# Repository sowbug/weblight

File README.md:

# WebLight

A USB-controlled LED designed for the
[WebUSB API](https://wicg.github.io/webusb/).

Try the web app
===
Have a WebLight device already?  
Launch the web app here:  
https://sowbug.github.io/weblight/

What does the javascript look like to write color values?  
Check out [software/src/weblight-card.html](https://github.com/sowbug/weblight/blob/master/software/src/weblight-card.html)

Developing WebLight Devices
===

Toolchain/environment setup
---

* Install avr-gcc. On Windows, download avr-gcc from
http://andybrown.me.uk/2015/03/08/avr-gcc-492/. Make sure you've
installed a base MinGW and MSYS system or equivalent, and have them in
your system path. On Linux, try something like `sudo apt-get install
gcc-avr binutils-avr gdb-avr avr-libc avrdude`. On OS X,
[CrossPack](https://www.obdev.at/products/crosspack/index.html) works.
* Install libusb. `sudo apt-get install libusb-dev` works on
  Linux, and `brew install libusb libusb-compat` works on OS X.
* Install pyusb. `sudo apt-get install python-usb` on Linux, or `sudo pip
  install pyusb` on other platforms.
* Build and install the
  [micronucleus command-line tool](https://github.com/micronucleus/micronucleus/tree/master/commandline)
  to be able to upload to the ATTiny85. Have it somewhere in your PATH. Don't forget [the udev rule](https://raw.githubusercontent.com/micronucleus/micronucleus/master/commandline/49-micronucleus.rules) if needed.
* Copy the files in `udev` to `/etc/udev/rules.d/` and then `sudo
  udevadm control --reload-rules`.

Programming a newly built board
---

* Connect a 6-pin AVR programmer. Note that if you've built the
  production version of the board, you'll need either an SOIC-8 clip
  manually wired for the ATtiny85, or else a
  [ProtoProg](http://protofusion.org/wordpress/2013/05/open-hardware-pogo-pin-programmer/)
  programming
  adapter. [This is the project I ordered](https://oshpark.com/shared_projects/fqvxyzoH)
  from OSH Park, and you'll want [0.68mm diameter, 16mm length pogo
  pins](http://www.ebay.com/sch/i.html?_trksid=p3984.m570.l1313.TR0.TRC0&_nkw=%09+10pcs+P50-J1+Dia+0.68mm+Length+16mm+75g+Spring+Test.&_sacat=0&_from=R40), probably from eBay.
* `cd firmware`
* Configure the makefile to talk to your type of programmer (default
usbtiny).
* `make factory` Now you have a bootloader-ready board with no firmware.
* Disconnect the programmer and plug it into a USB port.
* `make clean upload`

Mass-producing boards
---

This clones the complete firmware from an existing device. For
convenience, a relatively stable version of that complete firmware
image is already here in the repository (full-[version].hex). If you
overwrite it, we'll assume you know what you're doing.

1. Make one device using the instructions from the previous section.
1. Unplug from USB and attach to programmer.
1. `cd firmware`
1. `make create_full` This clones the firmware of the board you just
built.
1. Attach your next board to the programmer.
1. `make factory_mp`
1. Repeat last two steps for all remaining boards.

Development
---

1. In the `firmware` directory, `make clean upload`.
1. Plug in the board. After a few moments you should see `Micronucleus
   done. Thank you!`
1. Now the lights on the board should run a startup sequence.
1. Using `lsusb` you should see something like `Bus 001 Device 006: ID
   1209:a800 InterBiometrics`.

Usage
---

1. Install [PyUSB](http://walac.github.io/pyusb/). `sudo pip install
pyusb==1.0.0.b2`
1. From the base directory of the weblight project,
`./commandline/wlctl 800000` will give you a medium-brightness red
light (it uses CSS-style RGB color format).
1. `--help` for more options.

BOM for production (not developer) circuit
---

The best results are with an ENIG finish 2.0mm thickness PCB. If you're just prototyping, 1.6mm will work, but you'll want to put some thick solder on the USB leads to bulk them up a bit. Even then, the fit in the USB socket will be loose. ENIG takes longer to wear out than regular HASL.

The board measures 12mm x 41.1734mm x 2.0mm.

* C1: 1uF 0805 capacitor (DigiKey 311-1365-1-ND)
* C2: 0.1uF 0805 capacitor (DigiKey 311-1142-1-ND)
* D1, D2: 3.6V SOD-323 Zener diode. I successfully used BZT52C3V6S-7-F and MM3Z3V6T1G (DigiKey MM3Z3V6T1GOSCT-ND). According to [V-USB Hardware Considerations](http://vusb.wikidot.com/hardware), they should be "those that look like 1N4148 (usually 500 mW or less)"
* D3, D4: low forward-voltage SOD-323 diode (0.4-volt or less forward voltage so that the supply to the LEDs is higher than 4.5 volts). I have successfully used Toshiba 1SS367 (forward voltage about 0.3V, DigiKey 1SS367H3FCT-ND).
* LED1, LED2: APA102C LED (Real versions of these are not especially easy to find)
* R1: 1.5K 0805 resistor (DigiKey 311-1.5KARCT-ND)
* R2, R3: 68 0805 resistor (DigiKey 311-68ARCT-ND)
* R4: 10K 0805 resistor (DigiKey 311-10KARCT-ND)
* U1: ATtiny85 ATTINY85-20SU (DigiKey ATTINY85-20SURCT-ND)

Tips
---

* In addition to `wlctl` in the `commandline` directory, there is
`lswusb`, which attempts to parse WebUSB descriptors. This utility
will help you when you're developing your own WebUSB-compatible
device.

FAQ
===

* **What is WebUSB?** It's a [new web
  standard](https://reillyeon.github.io/webusb/) that makes it
  easy to write a USB driver once (in JavaScript) and have it work
  everywhere that WebUSB is supported.

* **Aren't there already a lot of USB-controlled lights out there?**
  Yes, it's more or less a rite of passage in hobbyist electronics to
  make some kind of blinking light. The purpose of this project was to
  design a very simple WebUSB device that might actually be useful.

* **You said "useful" in the prior answer. Please define that.** A
  WebUSB-enabled light can alert you of interesting things, like a
  broken continuous build, a service interruption, or yet another
  crash in the price of bitcoin.

* **Which board should I build?** If you're interested in hacking on
  the firmware, build
  [`weblight_developer.brd`](https://github.com/sowbug/weblight/blob/master/hardware/weblight_developer.brd). This
  one has a few more features that make firmware development more convenient. Otherwise if
  you just want a device to play with, build
  [`weblight.brd`](https://github.com/sowbug/weblight/blob/master/hardware/apa102/weblight.brd). That
  one is more compact, but it requires the ProtoProg ISP adapter, rather than the more common
  AVRISP 6-pin adapter. Both designs use 0805 SMT components. Either board can be ordered from [OSH Park](https://oshpark.com/) or [Seeed](https://www.seeedstudio.com/service/). Note that if you manufacture with a
  standard 1.6mm PCB, you'll have to solder the contacts to give them enough thickness to connect. For end-user
  boards, 2.0mm or 2.4mm will fit better in USB sockets, and ENIG finish will last longer without tarnishing.

* **I don't want to build a board, but I'd like one. Will you sell me one?** I don't have plans to mass-produce boards for sale. But if you're interested in getting one, [subscribe to notifications for this issue](https://github.com/sowbug/weblight/issues/31).

* **I remember reading something about Origin Trials. What does that have to do with WebUSB?** Chrome 61 and beyond ship with WebUSB, so if your users are running up-to-date Chrome, you're all set! But in case you're curious, the Chrome team has a system called Origin Trials for gathering real developer feedback on provisional APIs. Go to https://bit.ly/OriginTrials to learn more.

Acknowledgments
===

* Jenna Fox ([bluebie](https://github.com/bluebie)) and Tim ([cpldcpu](https://github.com/cpldcpu/)) for micronucleus advice. (Update December 2016: [Tim's article about SK9822](https://cpldcpu.com/2016/12/13/sk9822-a-clone-of-the-apa102/).)
* bobhackmelb on freenode for advice on PCB manufacturing, specifically thickness.
* [Passerby](http://electronics.stackexchange.com/users/17178/passerby) for help [reverse-engineering](http://electronics.stackexchange.com/questions/209941/two-sided-connectorless-usb-on-a-pcb) the double-sided USB connector.
* [gerblook.org](http://gerblook.org/) for an awesome Gerber visualizer.
* [Lars Knudsen](https://github.com/larsgk) for keeping docs up to date.

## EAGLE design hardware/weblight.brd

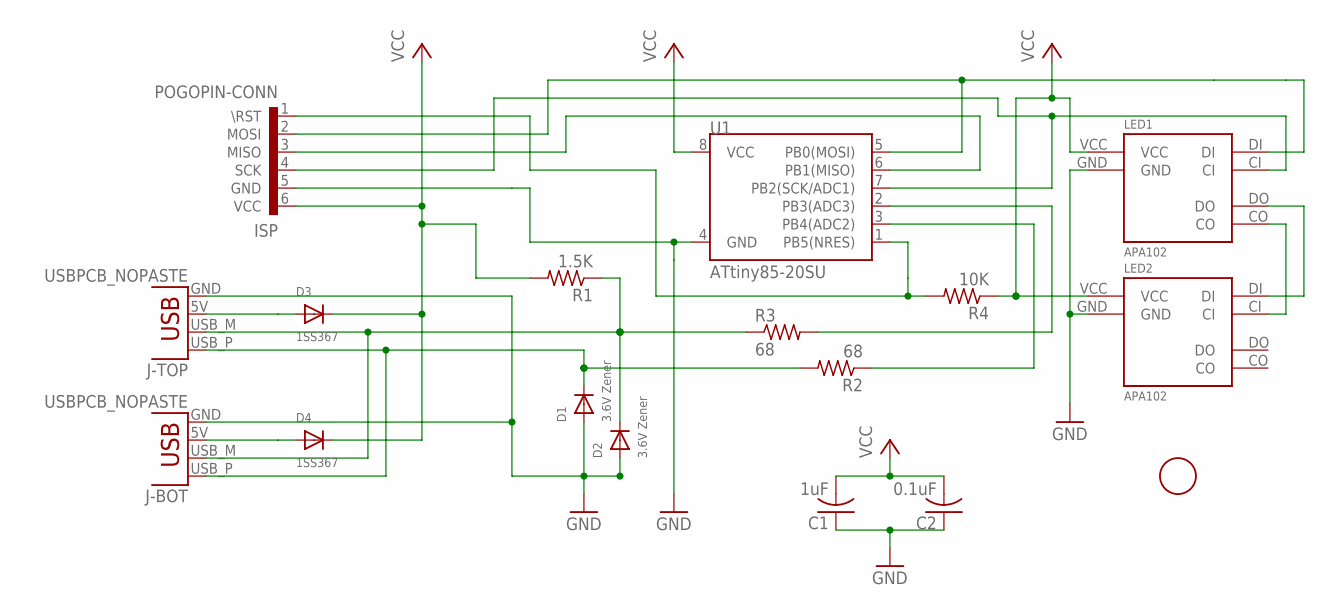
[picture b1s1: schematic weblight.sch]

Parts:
C1: 1uF; C0805
C2: 0.1uF; C0805
D1, D2: 3.6V Zener; SOD-323
D3, D4: 1SS367; SOD-323
FID1: FIDUCIAL; FIDUCIAL_1MM
ISP: POGOPIN-CONN; POGOPROG-CONN-OH-SMALLERVIAS-NOCREAM
J-BOT: USBPCB_NOPASTE; USB-A-PCB-NOPASTE
J-TOP: USBPCB_NOPASTE; USB-A-PCB-NOPASTE
LED1, LED2: APA102
R1: 1.5K; R0805
R2, R3: 68; R0805
R4: 10K; R0805
U1: ATtiny85-20SU; SO08-EIAJ

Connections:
5V-BOT: D4.A, J-BOT.5V (VBUS)
5V-TOP: D3.A, J-TOP.5V (VBUS)
CLK_1/SCK: ISP.4 (SCK), LED1.CI, U1.7 (PB2(SCK/ADC1))
CLK_2: LED1.CO, LED2.CI
DIN_1/MOSI: ISP.2 (MOSI), LED1.DI, U1.5 (PB0(MOSI))
DIN_2: LED1.DO, LED2.DI
GND: C1.1, C2.1, D1.A, D2.A, ISP.5 (GND), J-BOT.GND, J-TOP.GND, LED1.GND, LED2.GND, U1.4 (GND)
MISO: ISP.3 (MISO), U1.6 (PB1(MISO))
N_RESET: ISP.1 (\RST), R4.2, U1.1 (PB5(NRES))
USB_D_MINUS: R3.2, U1.2 (PB3(ADC3))
USB_D_MINUS_RAW: D2.C, J-BOT.USB_M (D-), J-TOP.USB_M (D-), R1.1, R3.1
USB_D_PLUS: R2.1, U1.3 (PB4(ADC2))
USB_D_PLUS_RAW: D1.C, J-BOT.USB_P (D+), J-TOP.USB_P (D+), R2.2
VCC: C1.2, C2.2, D3.C, D4.C, ISP.6 (VCC), LED1.VCC, LED2.VCC, R1.2, R4.1, U1.8 (VCC)

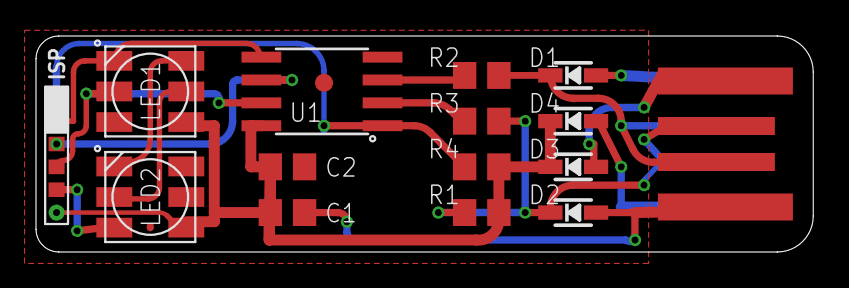
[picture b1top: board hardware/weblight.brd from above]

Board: 2 copper layers, 43.2 x 12.0 mm, 17 parts (1 on the bottom side), 14 nets.

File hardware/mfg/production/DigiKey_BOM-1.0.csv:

Digi-Key Part Number,Manufacturer,Manufacturer Part Number,Customer Reference,Quantity 1,Quantity 2,Quantity 3,Mfg Std Lead Time,Description,Comments,RoHS Status,Lead Free Status,REACH Status
311-1365-1-ND,YAGEO (VA),CC0805KKX7R7BB105,C1,1,0,0,21 Weeks,CAP CER 1UF 16V X7R 0805,Alternate Packaging Exists,RoHS Compliant,Lead free,Unaffected Dec-2015
311-1338-1-ND,YAGEO (VA),CC0402KRX7R7BB104,C2,1,0,0,23 Weeks,CAP CER 0.1UF 16V X7R 0402,Alternate Packaging Exists,RoHS Compliant,Lead free,Unaffected Dec-2015
MM3Z3V6T1GOSCT-ND,ON SEMICONDUCTOR (VA),MM3Z3V6T1G,"D1, D2",2,0,0,25 Weeks,DIODE ZENER 3.6V 300MW SOD323,Alternate Packaging Exists,RoHS Compliant,Lead free,Unaffected Dec-2015
1SS367H3FCT-ND,TOSHIBA SEMICONDUCTOR AND STORAGE (VA),"1SS367,H3F","D3, D4",2,0,0,10 Weeks,DIODE SCHOTTKY 10V 100MA SC76,Alternate Packaging Exists,RoHS Compliant,Lead free,Not Available
311-1.5KARCT-ND,YAGEO (VA),RC0805JR-071K5L,R1,1,0,0,22 Weeks,RES SMD 1.5K OHM 5% 1/8W 0805,Alternate Packaging Exists,RoHS Compliant,Lead free,Unaffected Dec-2015
311-68ARCT-ND,YAGEO (VA),RC0805JR-0768RL,"R2, R3",2,0,0,22 Weeks,RES SMD 68 OHM 5% 1/8W 0805,Alternate Packaging Exists,RoHS Compliant,Lead free,Unaffected Dec-2015
311-10KARCT-ND,YAGEO (VA),RC0805JR-0710KL,R4,1,0,0,22 Weeks,RES SMD 10K OHM 5% 1/8W 0805,Alternate Packaging Exists,RoHS Compliant,Lead free,Unaffected Dec-2015
ATTINY85-20SURCT-ND,ATMEL (VA),ATTINY85-20SUR,U1,1,0,0,6 Weeks,IC MCU 8BIT 8KB FLASH 8SOIC,Alternate Packaging Exists,RoHS Compliant,Lead free,Unaffected Dec-2015

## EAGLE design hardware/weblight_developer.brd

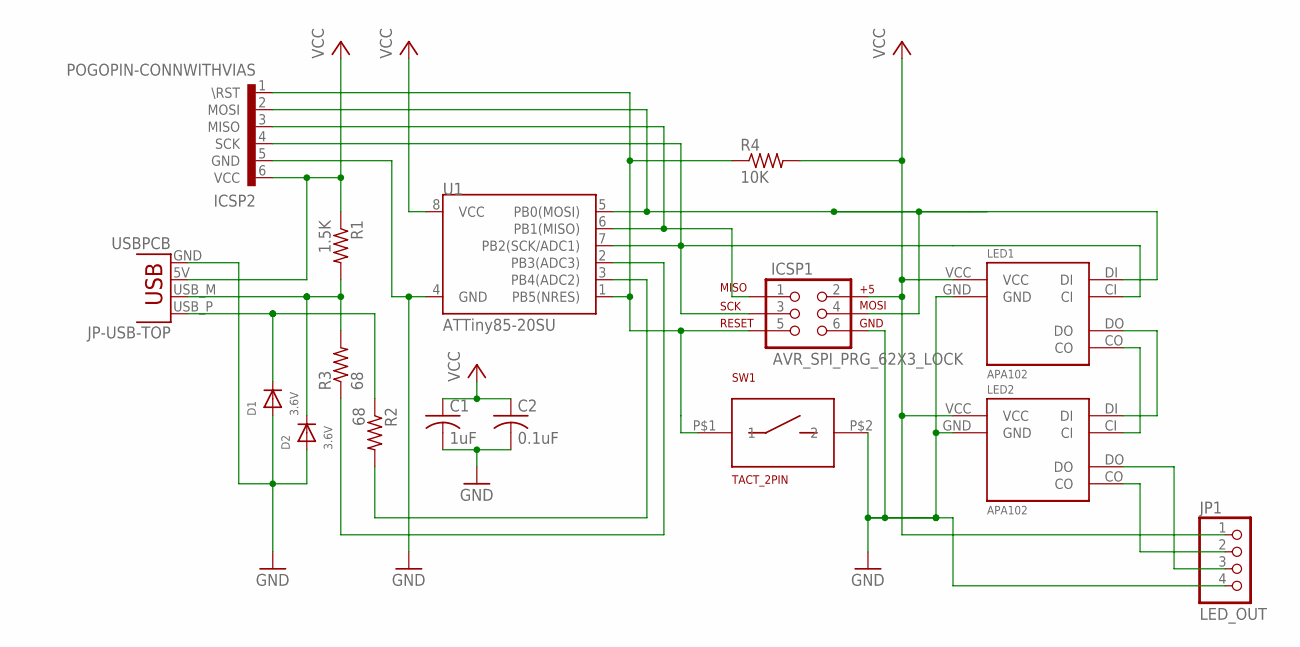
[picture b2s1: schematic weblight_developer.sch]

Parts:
C1: 1uF; C0805
C2: 0.1uF; C0805
D1, D2: 3.6V; SOD-323
ICSP1: AVR_SPI_PRG_62X3_LOCK; 2X3_LOCK
ICSP2: POGOPIN-CONNWITHVIAS; POGOPROG-CONN-0H
JP1: LED_OUT; 1X04_ROUND
JP-USB-TOP: USBPCB; USB-A-PCB
LED1, LED2: APA102
R1: 1.5K; R0805
R2, R3: 68; R0805
R4: 10K; R0805
SW1: TACT_2PIN; TD-85XU
U1: ATTiny85-20SU; SO08-EIAJ

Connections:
CLK_1/SCK: ICSP1.3, ICSP2.4 (SCK), LED1.CI, U1.7 (PB2(SCK/ADC1))
CLK_2: LED1.CO, LED2.CI
CLK_3: JP1.2, LED2.CO
DATA_1/MOSI: ICSP1.4, ICSP2.2 (MOSI), LED1.DI, U1.5 (PB0(MOSI))
DATA_2: LED1.DO, LED2.DI
DATA_3: JP1.3, LED2.DO
GND: C1.2, C2.2, D1.A, D2.A, ICSP1.6, ICSP2.5 (GND), JP1.4, JP-USB-TOP.GND, LED1.GND, LED2.GND, SW1.P$2 (2), U1.4 (GND)
MISO: ICSP1.1, ICSP2.3 (MISO), U1.6 (PB1(MISO))
N_RESET: ICSP1.5, ICSP2.1 (\RST), R4.1, SW1.P$1 (1), U1.1 (PB5(NRES))
USB_D_MINUS: R3.1, U1.2 (PB3(ADC3))
USB_D_MINUS_RAW: D2.C, JP-USB-TOP.USB_M (D-), R1.2, R3.2
USB_D_PLUS: R2.2, U1.3 (PB4(ADC2))
USB_D_PLUS_RAW: D1.C, JP-USB-TOP.USB_P (D+), R2.1
VCC: C1.1, C2.1, ICSP1.2, ICSP2.6 (VCC), JP1.1, JP-USB-TOP.5V (VBUS), LED1.VCC, LED2.VCC, R1.1, R4.2, U1.8 (VCC)

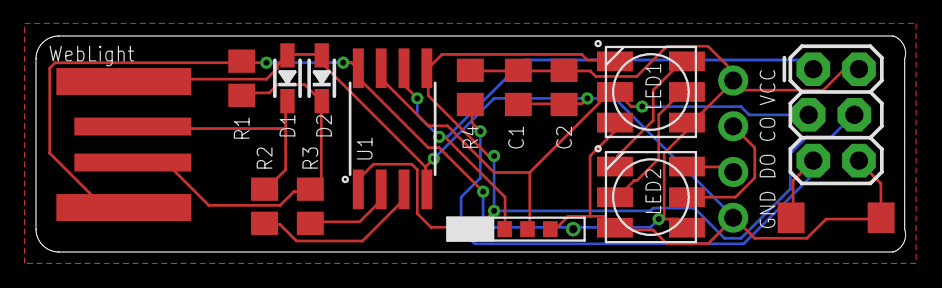
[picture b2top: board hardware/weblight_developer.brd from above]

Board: 2 copper layers, 48.3 x 12.0 mm, 16 parts (0 on the bottom side), 14 nets.

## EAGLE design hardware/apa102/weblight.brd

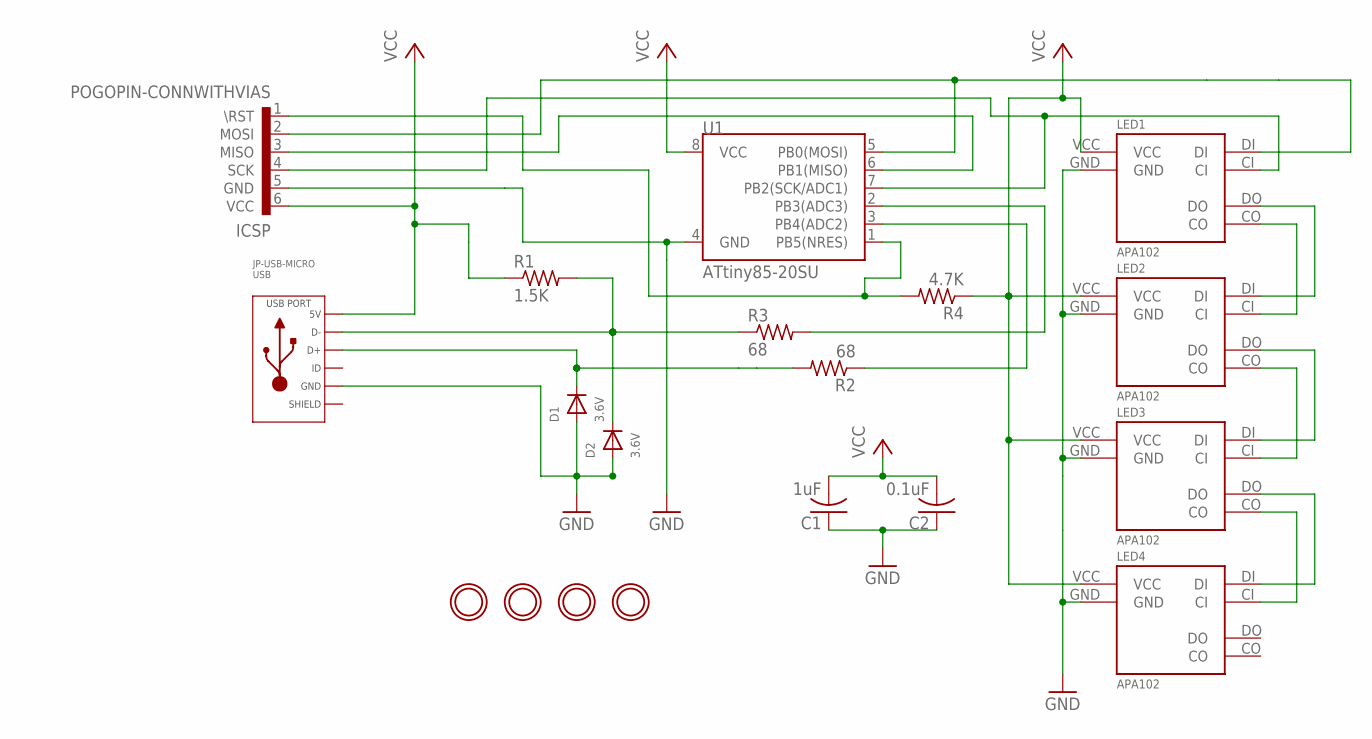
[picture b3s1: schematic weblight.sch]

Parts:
C1: 1uF; C0402
C2: 0.1uF; C0402
D1, D2: 3.6V; SOD-523
HOLE1, HOLE2, HOLE3, HOLE4: MOUNTINGHOLE2.0; MOUNTINGHOLE_2.0_PLATED
ICSP: POGOPIN-CONNWITHVIAS; POGOPROG-CONN-0H
JP-USB-MICRO: USB; MICROUSB-RIGHT
LED1, LED2, LED3, LED4: APA102
R1: 1.5K; R0402
R2, R3: 68; R0402
R4: 4.7K; R0402
U1: ATtiny85-20SU; SO08-EIAJ

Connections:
CLK_1/SCK: ICSP.4 (SCK), LED1.CI, U1.7 (PB2(SCK/ADC1))
CLK_2: LED1.CO, LED2.CI
CLK_3: LED2.CO, LED3.CI
CLK_4: LED3.CO, LED4.CI
DIN_1/MOSI: ICSP.2 (MOSI), LED1.DI, U1.5 (PB0(MOSI))
DIN_2: LED1.DO, LED2.DI
DIN_3: LED2.DO, LED3.DI
DIN_4: LED3.DO, LED4.DI
GND: C1.1, C2.1, D1.A, D2.A, ICSP.5 (GND), JP-USB-MICRO.5 (GND), LED1.GND, LED2.GND, LED3.GND, LED4.GND, U1.4 (GND)
MISO: ICSP.3 (MISO), U1.6 (PB1(MISO))
N_RESET: ICSP.1 (\RST), R4.2, U1.1 (PB5(NRES))
SLD: JP-USB-MICRO.S1 (SLD), JP-USB-MICRO.S2 (SLD), JP-USB-MICRO.S3 (SLD), JP-USB-MICRO.S4 (SLD), JP-USB-MICRO.S5 (SLD), JP-USB-MICRO.S6 (SLD)
USB_D_MINUS: R3.2, U1.2 (PB3(ADC3))
USB_D_MINUS_RAW: D2.K (C), JP-USB-MICRO.2 (D-), R1.2, R3.1
USB_D_PLUS: R2.1, U1.3 (PB4(ADC2))
USB_D_PLUS_RAW: D1.K (C), JP-USB-MICRO.3 (D+), R2.2
VCC: C1.2, C2.2, ICSP.6 (VCC), JP-USB-MICRO.1 (5V), LED1.VCC, LED2.VCC, LED3.VCC, LED4.VCC, R1.1, R4.1, U1.8 (VCC)

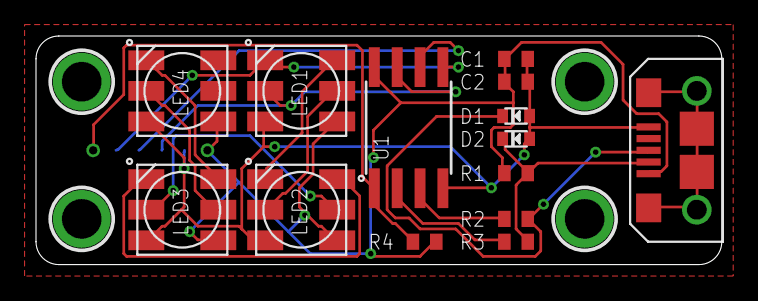
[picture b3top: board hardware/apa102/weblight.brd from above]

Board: 2 copper layers, 38.1 x 12.7 mm, 19 parts (1 on the bottom side), 17 nets.

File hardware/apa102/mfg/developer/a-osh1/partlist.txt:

Partlist

Exported from weblight_developer.sch at 11/15/15 4:37 PM

EAGLE Version 7.4.0 Copyright (c) 1988-2015 CadSoft

Assembly variant: 

Part       Value                 Device                Package          Library             Sheet

C1         10uF                  C-USC0805             C0805            rcl                 1
C2         0.1uF                 C-USC0805             C0805            rcl                 1
D1         3.6V                  DIODESOD-323          SOD-323          microbuilder        1
D2         3.6V                  DIODESOD-323          SOD-323          microbuilder        1
ICSP1      AVR_SPI_PRG_62X3_LOCK AVR_SPI_PRG_62X3_LOCK 2X3_LOCK         SparkFun-Connectors 1
ICSP2      POGOPIN-CONNWITHVIAS  POGOPIN-CONNWITHVIAS  POGOPROG-CONN-0H weblight            1
JP-USB-TOP USBPCB                USBPCB                USB-A-PCB        SparkFun-Connectors 1
JP1        LED_OUT               HEADER-1X4ROUND       1X04_ROUND       microbuilder        1
LED1       APA102                APA102                APA102           weblight            1
LED2       APA102                APA102                APA102           weblight            1
R1         1.5K                  R-US_R0805            R0805            rcl                 1
R2         68                    R-US_R0805            R0805            rcl                 1
R3         68                    R-US_R0805            R0805            rcl                 1
R4         4.7K                  R-US_R0805            R0805            rcl                 1
SW1        TACT_2PIN             TACT_2PIN             TD-85XU          weblight            1
U1         ATTiny85-20SU         ATTINY45TINY85-20-SMT SO08-EIAJ        SparkFun-DigitalIC  1

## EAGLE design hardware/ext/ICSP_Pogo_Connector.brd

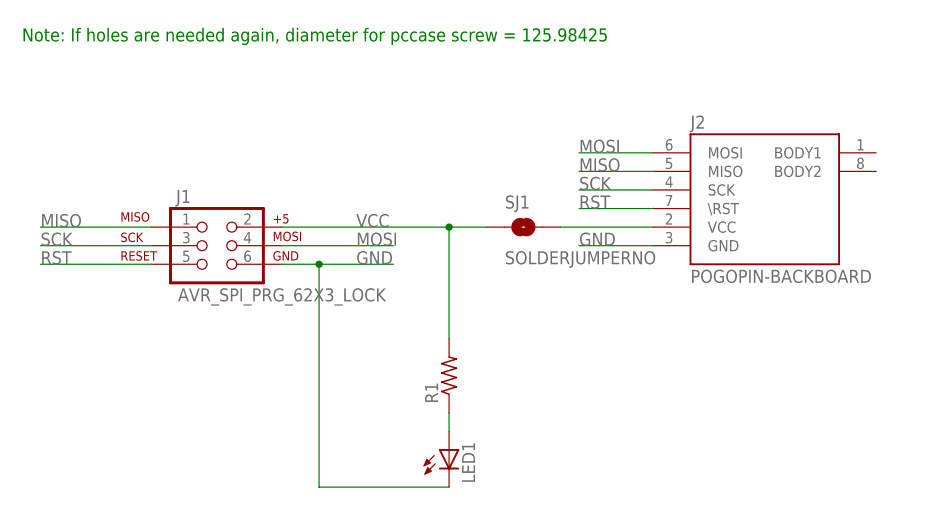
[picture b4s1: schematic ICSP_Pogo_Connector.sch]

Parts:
J1: AVR_SPI_PRG_62X3_LOCK; 2X3_LOCK
J2: POGOPIN-BACKBOARD; POGOPROG-BACKMOUNT
LED1: LED0603; LED-0603
R1: R-US_R0603; R0603
SJ1: SOLDERJUMPERNO; SJ_2S-NO

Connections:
GND: J1.6, J2.3 (GND), LED1.C
MISO: J1.1, J2.5 (MISO)
MOSI: J1.4, J2.6 (MOSI)
unnamed: J2.2 (VCC), SJ1.2
unnamed: LED1.A, R1.1
RST: J1.5, J2.7 (\RST)
SCK: J1.3, J2.4 (SCK)
VCC: J1.2, R1.2, SJ1.1

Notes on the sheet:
Note: If holes are needed again, diameter for pccase screw = 125.98425

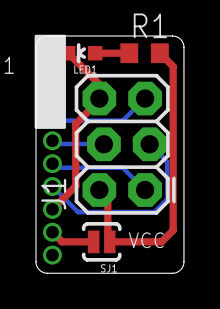
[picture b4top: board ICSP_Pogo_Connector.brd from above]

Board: 2 copper layers, 8.2 x 13.2 mm, 6 parts (1 on the bottom side), 8 nets.

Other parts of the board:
U$2: POGOPROG_LOGO

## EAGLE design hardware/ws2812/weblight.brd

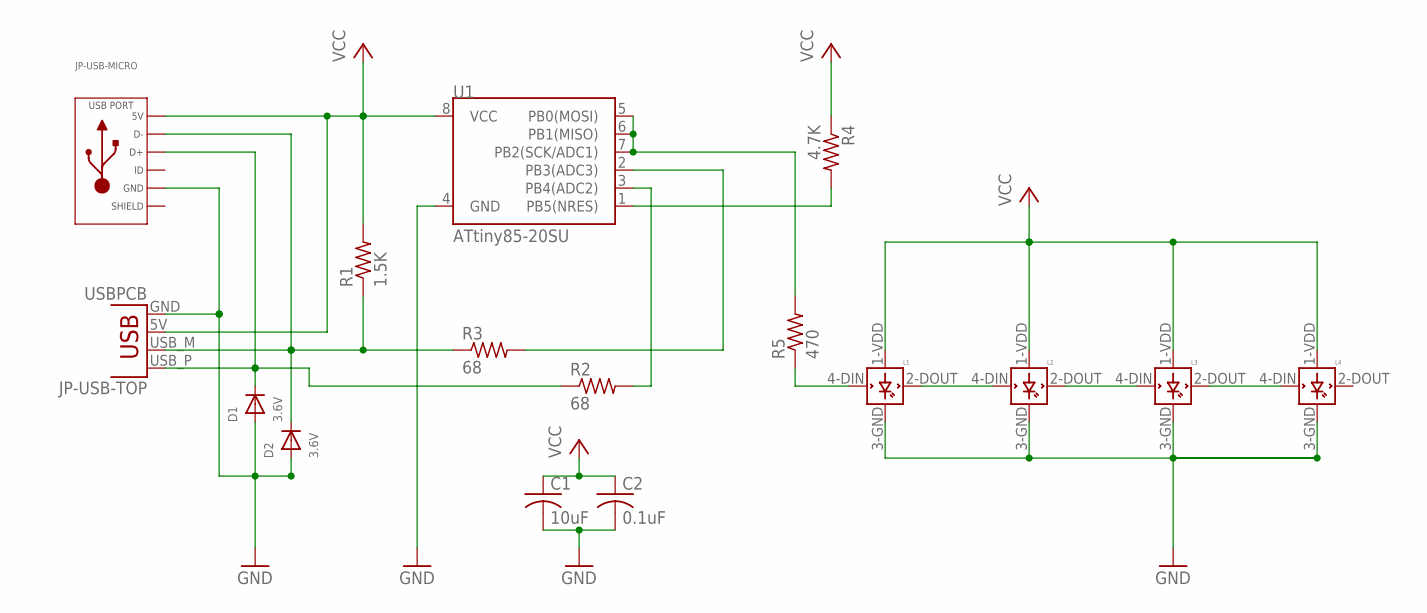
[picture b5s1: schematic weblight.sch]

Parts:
C1: 10uF; C0402
C2: 0.1uF; C0402
D1, D2: 3.6V; SOD-523
JP-USB-MICRO: USB_MICRO_RIGHT; MICROUSB-RIGHT
JP-USB-TOP: USBPCB; USB-A-PCB
L1, L2, L3, L4: WS2812B
R1: 1.5K; R0402
R2, R3: 68; R0402
R4: 4.7K; R0402
R5: 470; R0402
U1: ATtiny85-20SU; SO08-EIAJ

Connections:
DIN_1: L1.4-DIN (DIN), R5.1
DIN_2: L1.2-DOUT (DOUT), L2.4-DIN (DIN)
DIN_3: L2.2-DOUT (DOUT), L3.4-DIN (DIN)
DIN_4: L3.2-DOUT (DOUT), L4.4-DIN (DIN)
DIN_RAW: R5.2, U1.5 (PB0(MOSI)), U1.6 (PB1(MISO)), U1.7 (PB2(SCK/ADC1))
GND: C1.2, C2.2, D1.A, D2.A, JP-USB-MICRO.5 (GND), JP-USB-TOP.GND, L1.3-GND (GND), L2.3-GND (GND), L3.3-GND (GND), L4.3-GND (GND), U1.4 (GND)
N_RESET: R4.2, U1.1 (PB5(NRES))
SLD: JP-USB-MICRO.S1 (SLD), JP-USB-MICRO.S2 (SLD), JP-USB-MICRO.S3 (SLD), JP-USB-MICRO.S4 (SLD), JP-USB-MICRO.S5 (SLD), JP-USB-MICRO.S6 (SLD)
USB_D_MINUS: R3.2, U1.2 (PB3(ADC3))
USB_D_MINUS_RAW: D2.K (C), JP-USB-MICRO.2 (D-), JP-USB-TOP.USB_M (D-), R1.1, R3.1
USB_D_PLUS: R2.2, U1.3 (PB4(ADC2))
USB_D_PLUS_RAW: D1.K (C), JP-USB-MICRO.3 (D+), JP-USB-TOP.USB_P (D+), R2.1
VCC: C1.1, C2.1, JP-USB-MICRO.1 (5V), JP-USB-TOP.5V (VBUS), L1.1-VDD (VDD), L2.1-VDD (VDD), L3.1-VDD (VDD), L4.1-VDD (VDD), R1.2, R4.1, U1.8 (VCC)

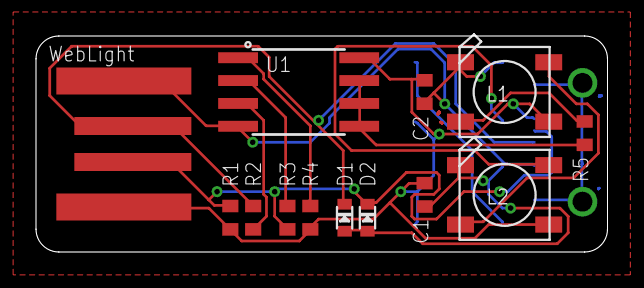
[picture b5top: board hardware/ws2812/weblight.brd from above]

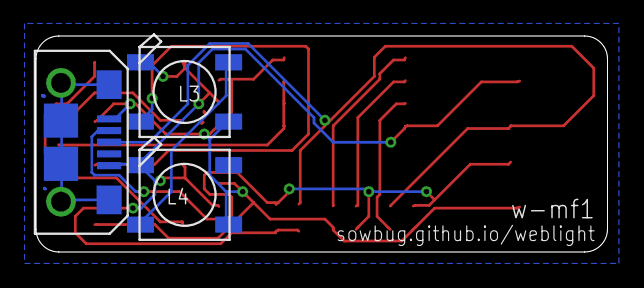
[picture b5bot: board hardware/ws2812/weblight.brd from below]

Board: 2 copper layers, 31.8 x 12.0 mm, 16 parts (3 on the bottom side), 13 nets.

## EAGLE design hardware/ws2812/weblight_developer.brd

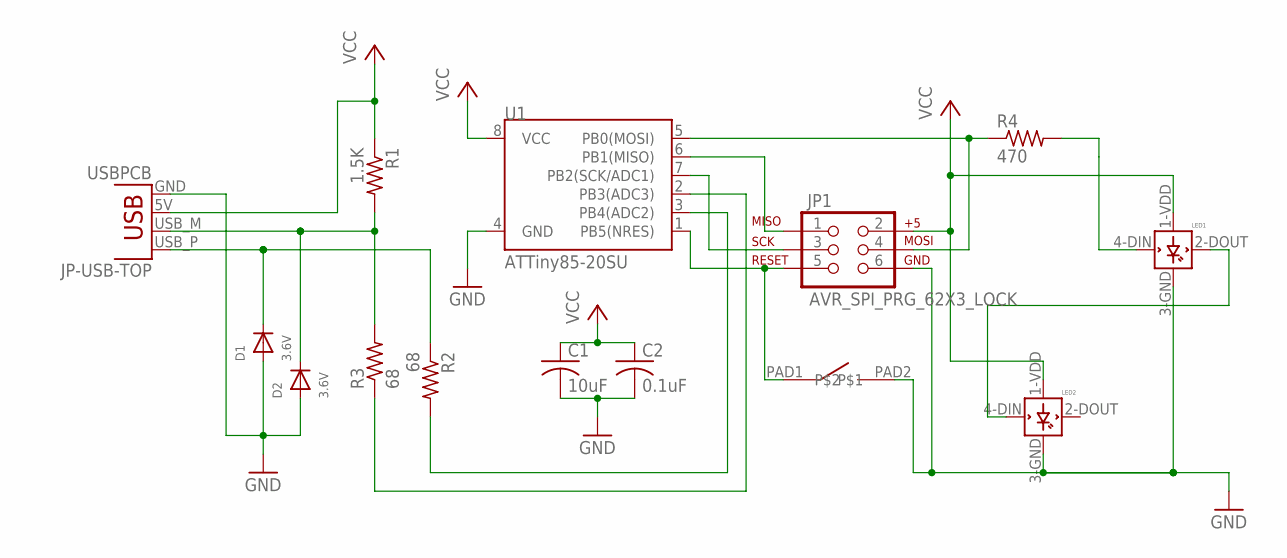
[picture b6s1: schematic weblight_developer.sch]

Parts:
C1: 10uF; C0805
C2: 0.1uF; C0805
D1, D2: 3.6V; SOD-323
JP1: AVR_SPI_PRG_62X3_LOCK; 2X3_LOCK
JP-USB-TOP: USBPCB; USB-A-PCB
LED1, LED2: WS2812B
R1: 1.5K; R0805
R2, R3: 68; R0805
R4: 470; R0805
SW_RESET: BUTTON_TD-85XU
U1: ATTiny85-20SU; SO08-EIAJ

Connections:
DIN_1: LED1.4-DIN (DIN), R4.2
DIN_2: LED1.2-DOUT (DOUT), LED2.4-DIN (DIN)
GND: C1.2, C2.2, D1.A, D2.A, JP1.6, JP-USB-TOP.GND, LED1.3-GND (GND), LED2.3-GND (GND), SW_RESET.PAD2, U1.4 (GND)
MISO: JP1.1, U1.6 (PB1(MISO))
MOSI/DIN_RAW: JP1.4, R4.1, U1.5 (PB0(MOSI))
unnamed: JP1.3, U1.7 (PB2(SCK/ADC1))
RESET: JP1.5, SW_RESET.PAD1, U1.1 (PB5(NRES))
USB_D_MINUS: R3.1, U1.2 (PB3(ADC3))
USB_D_MINUS_RAW: D2.C, JP-USB-TOP.USB_M (D-), R1.2, R3.2
USB_D_PLUS: R2.2, U1.3 (PB4(ADC2))
USB_D_PLUS_RAW: D1.C, JP-USB-TOP.USB_P (D+), R2.1
VCC: C1.1, C2.1, JP1.2, JP-USB-TOP.5V (VBUS), LED1.1-VDD (VDD), LED2.1-VDD (VDD), R1.1, U1.8 (VCC)

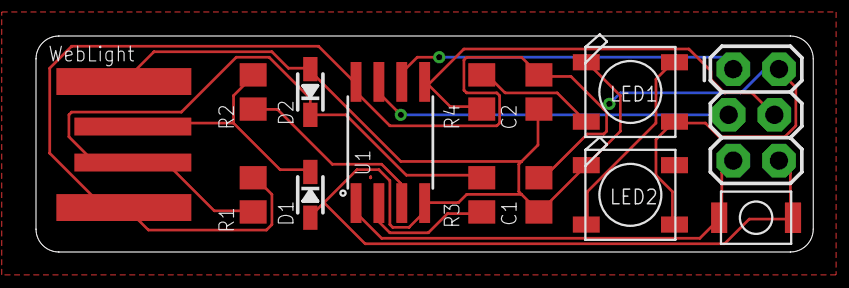
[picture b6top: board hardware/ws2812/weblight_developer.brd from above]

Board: 2 copper layers, 43.2 x 12.0 mm, 14 parts (0 on the bottom side), 12 nets.

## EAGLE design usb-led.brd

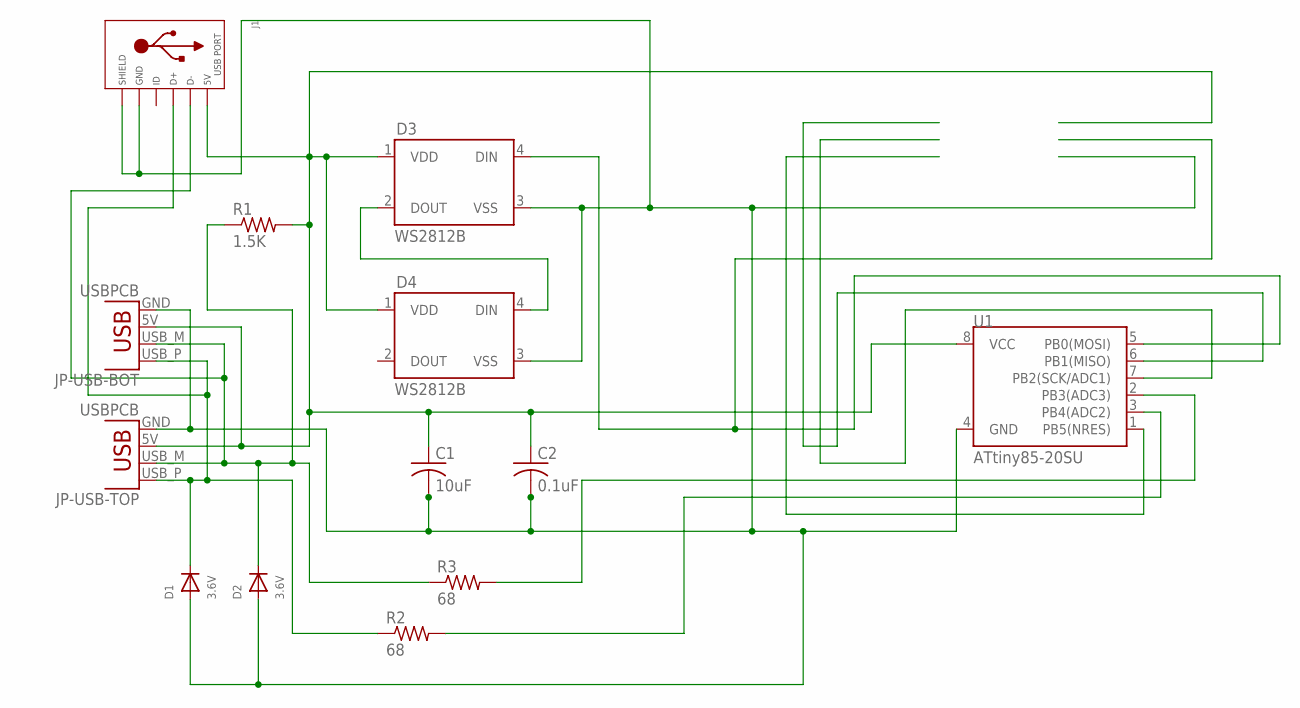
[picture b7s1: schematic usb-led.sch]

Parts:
C1: 10uF; C0402
C2: 0.1uF; C0402
D1, D2: 3.6V; SOD-523
D3, D4: WS2812B
J1: USB_MICRO_RIGHT; MICROUSB-RIGHT
JP-USB-BOT: USBPCB; USB-A-PCB
JP-USB-TOP: USBPCB; USB-A-PCB
R1: 1.5K; R0402
R2, R3: 68; R0402
U1: ATtiny85-20SU; SO08-EIAJ

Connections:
DIN_2: D3.2 (DOUT), D4.4 (DIN)
GND: C1.2, C2.2, D1.A, D2.A, D3.3 (VSS), D4.3 (VSS), J1.5 (GND), J1.S1 (SLD), JP-USB-BOT.GND, JP-USB-TOP.GND, U1.4 (GND); also elsewhere on the board
MISO: U1.6 (PB1(MISO)); also elsewhere on the board
MOSI/DIN: D3.4 (DIN), U1.5 (PB0(MOSI)); also elsewhere on the board
RESET: U1.1 (PB5(NRES)); also elsewhere on the board
SCK: U1.7 (PB2(SCK/ADC1)); also elsewhere on the board
USB_D_MINUS: R3.2, U1.2 (PB3(ADC3))
USB_D_MINUS_RAW: D2.K (C), J1.2 (D-), JP-USB-BOT.USB_M (D-), JP-USB-TOP.USB_M (D-), R1.1, R3.1; also elsewhere on the board
USB_D_PLUS: R2.2, U1.3 (PB4(ADC2))
USB_D_PLUS_RAW: D1.K (C), J1.3 (D+), JP-USB-BOT.USB_P (D+), JP-USB-TOP.USB_P (D+), R2.1; also elsewhere on the board
VCC: C1.1, C2.1, D3.1 (VDD), D4.1 (VDD), J1.1 (5V), JP-USB-BOT.5V (VBUS), JP-USB-TOP.5V (VBUS), R1.2, U1.8 (VCC); also elsewhere on the board

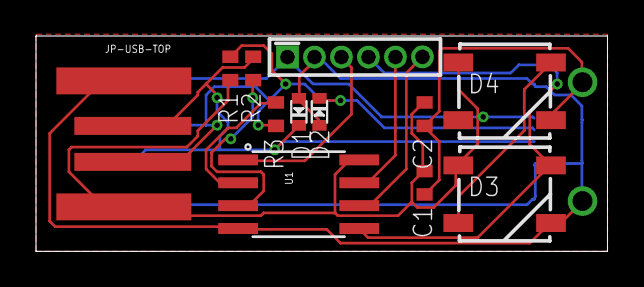
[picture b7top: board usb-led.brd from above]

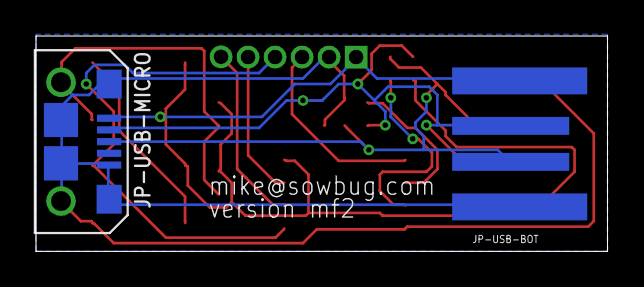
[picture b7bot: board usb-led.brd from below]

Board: 2 copper layers, 31.8 x 12.0 mm, 14 parts (2 on the bottom side), 11 nets.

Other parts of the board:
JP-ISP: AVR_MINI_PROGSMD; AVR_MINI_PROG
JP-USB-MICRO: MICROUSB-RIGHT

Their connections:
GND: JP-ISP.2, JP-USB-MICRO.5, JP-USB-MICRO.S1, JP-USB-MICRO.S2, JP-USB-MICRO.S3, JP-USB-MICRO.S4, JP-USB-MICRO.S5, JP-USB-MICRO.S6; also elsewhere on the board
MISO: JP-ISP.6; also elsewhere on the board
MOSI/DIN: JP-ISP.4; also elsewhere on the board
RESET: JP-ISP.3; also elsewhere on the board
SCK: JP-ISP.5; also elsewhere on the board
USB_D_MINUS_RAW: JP-USB-MICRO.2; also elsewhere on the board
USB_D_PLUS_RAW: JP-USB-MICRO.3; also elsewhere on the board
VCC: JP-ISP.1, JP-USB-MICRO.1; also elsewhere on the board

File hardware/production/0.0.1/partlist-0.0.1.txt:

Partlist

Exported from usb-led.sch at 9/28/2015 10:41 PM

EAGLE Version 7.4.0 Copyright (c) 1988-2015 CadSoft

Assembly variant: 

Part       Value                 Device                Package   Library             Sheet

C1         10uF                  C-USC0805             C0805     rcl                 1
C2         1uF                   C-USC0805             C0805     rcl                 1
D1         3.6                   DIODESOD-323          SOD-323   microbuilder        1
D2         3.6                   DIODESOD-323          SOD-323   microbuilder        1
D3         WS2812B               WS2812B               WS2812B   SparkFun-LED        1
D4         WS2812B               WS2812B               WS2812B   SparkFun-LED        1
JP-ISP     AVR_SPI_PRG_62X3_LOCK AVR_SPI_PRG_62X3_LOCK 2X3_LOCK  SparkFun-Connectors 1
JP-USB-BOT USBPCB                USBPCB                USB-A-PCB SparkFun-Connectors 1
JP-USB-TOP USBPCB                USBPCB                USB-A-PCB SparkFun-Connectors 1
R1         1K5                   R-US_R0805            R0805     rcl                 1
R2         68                    R-US_R0805            R0805     rcl                 1
R3         68                    R-US_R0805            R0805     rcl                 1
U1         Tiny85-20-SMT         ATTINY45TINY85-20-SMT SO08-EIAJ SparkFun-DigitalIC  1

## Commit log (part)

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2015-10-05 Add micronucleus version of usbdrv.
    Added
    https://github.com/micronucleus/micronucleus/tree/master/firmware/usbdrv
    as of d59e4e6f23a2bccba9c2a68a315ebf394a17f914.
2015-10-05 New broken stuff
2015-10-14 Update name; add Linux setup instructions.
2015-10-14 Adapt VUSB custom-class sample to this project. Does nothing
2015-10-14 Update README with very basic development instructions.
2015-10-15 Rename
2015-10-15 Rename directory to production
2015-10-19 State machine; colorful startup
2015-10-19 Remove debugging/add docs
    - Take out oddebug.h, which I don't think the t85 supports.
    - Add `make clean && make hex && micronucleus --run main.hex` magic to
    Makefile header.
2015-10-19 Refactor state machine
2015-10-19 Forgot about RC oscillator calibration
2015-10-19 Cleanup. USB is still flaky.
2015-10-20 Python script drives RGB
2015-10-21 Add BOS descriptor. Next: WebUSB descriptors
2015-10-21 Cleanup -- still not working
2015-10-21 Turn weblight tool into diagnostic thingie
2015-10-21 More
2015-10-21 Return vendor/product string
2015-10-21 Whoops
2015-10-21 16d0 for micronucleus. 16c0 for shared VUSB PID
2015-10-21 Change name and landing
2015-10-21 Miscounted descriptor length (includes self)
2015-10-21 Initial
2015-10-21 Try USBConnectionEvent
2015-10-22 Handle disconnection
2015-10-23 Add images
2015-10-23 Fix image link
2015-10-23 Link to spec
2015-10-24 #8: Add serial number
2015-10-24 Update to https://github.com/obdev/v-usb 3920204
2015-10-24 Partly address #13 by scheduling light update after TX is done
2015-10-25 Spacing
2015-10-26 #2: Remove bottom USB connector to avoid short
2015-10-26 #17: add 470 ohm resistor before first DIN
2015-10-26 Changes to prod circuit.
2015-10-26 Developer board changes.
    Convert every 0402 SMD to 0805.
2015-10-26 Export from schematic -- looks nicer
2015-10-26 mf3 rc1
    Pullup resistor on NRES
2015-10-26 #19: Update prod label
2015-10-26 Include new --reset trick in README
2015-10-26 Turn off all LEDs when count changes
2015-10-26 Specify VID/PID in wlctl
2015-10-26 Improved README
2015-10-27 Cute overload: blink 3x before reset
2015-10-27 Renumber requests
2015-10-27 More VID/PID change work
2015-10-27 Log mfgr/product/serial
2015-10-27 Clean up use of readLoop, which I don't understand
2015-10-27 Poor man's redirect to HTTPS
    See http://stackoverflow.com/questions/4723213/detect-http-or-https-then-force-https-in-javascript
2015-10-27 Typo - doh
2015-10-27 Get right host
2015-10-27 Steal from http://www.getmdl.io/
2015-10-27 First pass at WinUSB descriptor (doesn't work yet)
2015-10-28 Fix typo
2015-10-28 That trick didn't work.
2015-10-28 Turn off LEDs before StatusBlink.
2015-10-29 Maybe fix #20 (WinUSB)
    https://social.msdn.microsoft.com/Forums/sqlserver/en-US/ae64282c-3bc3-49af-8391-4d174479d9e7/microsoft-os-20-descriptors-not-working-on-an-interface-of-a-composite-usb-device?forum=wdk
    QUOTE
    It looks like we'll need to update the MSOS 2.0 Descriptor docs to match
    the implementation in USBCCGP. The bConfigurationValue in the
    configuration subset header should actually just be an index value, not
    the configuration value.
2015-10-29 More comments to follow along
2015-10-29 Add APA102C datasheet
2015-10-30 Add Seeed OPL; rearrange lbr
2015-10-31 Finish refactor of main.c -> webusb.c
2015-10-31 Fix #15: read descriptors from PROGMEM to usbFunctionSetup()
2015-10-31 Interesting: PROGMEM makes WebUSB (not WinUSB) fail. Reverted
2015-10-31 Mention APA102C in next steps
2015-10-31 Manufacturing
2015-11-01 New Adafruit library
2015-11-01 *.l#*
2015-11-01 Miter board
2015-11-01 Fix zoom
2015-11-01 Add TODO about being friendlier with delays
2015-11-01 More work on #13 with many thanks to @Bluebie.
    - Remove USB_POST_TX_HOOK, which was the right idea but could be
    done more frequently after *any* frame from the host.
    - Switch interrupt to D- per V-USB advice in usbconfig.h to enable
    start-of-frame counter.
    - Enable USB_COUNT_SOF.
    - After usbPoll() in main loop, check sofCount and do LED work if it
2015-11-02 Move around stuff to split out WS2812 and APA102 versions
2015-11-02 Add FCI 10118193-0001LF part
2015-11-02 Adjust ground planes
2015-11-02 Handle multiple devices and don't do silly stuff with promises
2015-11-02 Startup sequence was getting annoying. Shortened
2015-11-03 Not so bright
2015-11-03 Removed duplicate --run argument that I've not noticed all this time
2015-11-03 Improve timing logic
2015-11-07 Random blink interval so it's easier to demo multiple lights.
2015-11-07 Remove probably superfluous code. But why does first transfer fail?
2015-11-15 Adapt to APA102
2015-11-15 Update README: APA102C
2015-11-15 Thanks http://protofusion.org/
2015-11-16 a-osh1
2015-11-16 Give Seeed a try
2015-11-16 Simpler startup. Remove start-of-frame stuff
2015-11-17 New pix
2015-11-17 New pic
2015-11-17 Re #15: y u no work?
2015-11-17 Better documentation
2015-11-17 Color picker
2015-11-17 Match up element
2015-11-17 Move template element to HTML
2015-11-17 Typo
2015-11-17 log again
2015-11-17 fix element variable name
2015-11-17 Clean up old cycling code
2015-11-17 cache => 4
2015-11-17 Break; white
2015-11-17 cache => 5; remove stray console log output
2015-12-06 Stencil files
2015-12-06 Remove old sketch
2015-12-07 Temp substitute of allowed origin
2015-12-10 Add factory_mp target
2015-12-10 Photo of a-seeed1
2015-12-10 Fix make bug and remove WS2812 references
2015-12-14 checkpoint
2015-12-16 Fix target name
2015-12-16 .hex for production
2015-12-23 WL_REQUEST_SET_RGB_SEQUENCE
2015-12-24 Convert to more robust sequencing approach
2015-12-24 Replace deleted line
2015-12-24 Forgot to save file
2015-12-24 Moved program location in EEPROM to flash faster.
2015-12-25 Faster programming
2015-12-25 Rough transition. Need to fix fixed-point math
2015-12-25 Fix transition math. Currently too big to flash
2015-12-25 Demo includes linear fade transition
2015-12-25 Half-fixed bug where COLOR doesn't work if transition sequence is happening
2015-12-25 Maybe fix #25
    Read http://www.nongnu.org/avr-libc/user-manual/pgmspace.html and learn
    that I've been doing it all wrong.
2015-12-25 Likely fix #25: USB_CFG_LONG_TRANSFERS had something to do with it
2015-12-25 Update factory images
2015-12-25 Comment
2015-12-25 mf2 production 0805 - ordered from OSH & Seeed
2015-12-26 NRES pullup 10K; big cap 1uF
2015-12-26 More help text
2015-12-26 Promote issue for getting boards
2015-12-26 Switch to new EEPROM update functions
2015-12-26 Fix #30: let hardware version bubble up from Makefile
2015-12-26 Move code into App
2015-12-26 Remove lame comment
2015-12-27 Moved to version 0.9 to better represent state of things
2016-01-08 Connectorless USB, longer board. Unrouted.
    - Two diodes to protect back connector. Thanks Passerby
    http://electronics.stackexchange.com/q/209941/84391
    - Moved C1/C2 closer to where they matter.
    - A few astute layout changes to facilitate future routing.
2016-01-08 Some manual routing. Mess
2016-01-12 bobhackmelb - thx
2016-01-16 More for #23: now allowed origins are configurable
2016-01-17 Better initial layout. Unrouted
2016-01-17 Checkpoint. Not all routed yet
2016-01-17 Checkpoint #3, some connectors
2016-01-17 Checkpoint #4, one airwire left
2016-01-17 Mitering
2016-01-17 Move labels around
2016-01-18 Fix #10: add WL_REQUEST_RESET_WATCHDOG
2016-01-18 Remove one more needless kink
2016-01-19 0.9.2.0 + http://www.hackvana.com/ files
2016-01-19 Remove tCream from ProtoProg footprint
2016-01-20 Other APA102C datasheet; 1SS367 Schottky diode datasheet
2016-01-20 Latest BOM
2016-01-22 Fix #32. 0.9.3
2016-02-13 Add a link that calls navigator.usb.requestDevice().
    Before a site can access a device it must request permission.
2016-02-13 Provide a set of device filters to navigator.usb.requestDevice().
    This parameter is not optional.
2016-03-01 Better production board description
2016-03-05 More acks
2016-03-26 Updated factory hex
2016-03-26 Link to new pic
2016-03-28 Update weblight.js for new selectConfiguration() API.
    The WebUSB API was updated to rename setConfiguration() to
    selectConfiguration() and provide the current configuration as an
    attribute instead of having a getConfiguration() method.
2016-03-28 Increment the cache to version 6.
2016-04-08 Add Origin Trial keys for the WebUSB experiment.
2016-04-14 Add new format Origin Trial tokens.
    The old format tokens will be removed later.
2016-05-19 Bump cache version to 8.
2016-08-21 Add fiducials. Move bottom text. Handle DirtyPCB DRU. Ver 1.0
2016-08-21 1.0 with blank soldermask images
    See https://github.com/hadleyrich/GerbLook/issues/15 for issue
2016-08-23 Panelized Gerbers
    3x10 using 145x140mm frame.
    http://blog.thisisnotrocketscience.nl/projects/pcb-panelizer-beta/
2016-08-23 .gerberset
2016-08-26 Fix #39: one fiducial under U1; 1.0.1
2016-08-27 Demote 1.0 to 1.0-rc1
2016-08-27 Flip ISP; hide fiducial; real 1.0 (I hope)
2016-08-27 1.0 as sent to PCBCart for quotation
2016-08-28 Update factory ROM
2016-08-28 Default program/serial if no EEPROM
2016-08-31 Update Origin Trial keys.
2016-09-14 Regenerate serial number via wlctl
2016-09-14 Update to 1.0 with new factory hex
2016-09-16 Rebuild 1.0 hex with new micronucleus
2016-09-16 Update hex
2016-09-16 PCBCart assembly instructions
2016-09-16 Update instructions to include video https://youtu.be/knSyfHsJjvY
2016-09-30 Add board dimensions.
2016-11-11 Grrr, hack around flaky probably fake APA102C
2016-11-11 Strength-reduction of fake APA102C hack
2016-11-12 Further SK9822 hacking.
    https://cpldcpu.wordpress.com/2014/11/30/understanding-the-apa102-superled/
    comments provided further insight. Still not sure if this is correct.
2016-11-22 Dynamic descriptor set (progression of b92d63f). gen_eeprom untested
2016-11-22 Indent error
2016-11-27 One-size-fits-all code for APA102C and SK9822.
    Thanks Tim! https://github.com/cpldcpu/light_ws2812/commit/a1ee7aff2dfbdc1e690d5f129e2fbd0f086f8747
2016-12-04 SK9822 datasheet
2016-12-09 new spec link
2016-12-12 Rest of WebUSB parsing. Hacky
2016-12-13 Update to latest https://github.com/cpldcpu/light_ws2812
2016-12-13 Add link to Tim's article
2016-12-15 Move contents of gh-pages into docs subdirectory.
2017-01-26 origin trial => 2017/03/01
2017-02-24 add another webusb token
2017-03-07 Clean up origin trial tokens and add for M57+
2017-03-07 CACHE_VERSION 11
2017-03-07 Better link
    @chasej
2017-03-29 Update Origin Trial tokens.
    Note, I am not longer including tokens for localhost. To enable WebUSB
    in Chrome for development servers enable "experimental web platform
    features" in chrome://flags.
2017-04-11 Add new opcodes for selecting which LEDs to modify.
    SetLEDs now takes a 16-bit mask, allowing callers to select
    any combination of the first 15 LEDs for subsequent color
    ops. (Bit 1 is led[0] and so on.) The special mask value
    SELECT_ALL_LEDS (0xFFFFFFFF) is special and selects every
    LED available even if there are more than 15.
    Test: wlctl --select_leds 0,1 0x400000 # set leds 0 and 1 to red
2017-05-09 Update Origin Trial token
2017-05-16 Update webusb token
2017-07-31 Origin trial token update -> 2017-09-05
2017-10-12 Remove outdated origin trial token.
2017-10-20 Serve new Polymer 2 based app
    Built from commit 9b076a29e5f7e669b80c7b8636682b80b21c6d86.
2017-10-20 Add trailing slash to base path
    Build from commit d81bf1d1888a4daf362512e168f2ac00071644f2.
2017-10-21 Update README.md
    Update image and WebUSB specification links.
2017-10-21 Remove images
2017-10-21 Remove docs folder
    https://sowbug.github.io/weblight is now served from the gh-pages
    branch.
2017-11-27 Add pyusb install step to README.
2017-12-29 Implement LED selection when setting color
2018-01-03 add command line support
2018-03-12 Added reference to micronucleus udev

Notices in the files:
parts and their libraries:
microbuilder: This work is placed in the public domain, and may be freely used for commercial and non-commercial work with the following conditions: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
SparkFun-DigitalIC: Licensing: Creative Commons ShareAlike 4.0 International - https://creativecommons.org/licenses/by-sa/4.0
